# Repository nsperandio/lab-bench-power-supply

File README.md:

# lab-bench-power-supply (Work in progress, not ready yet).
A lab bench power supply made with a switching pre-regulation stage (tracking) followed by a custom linear regulator.

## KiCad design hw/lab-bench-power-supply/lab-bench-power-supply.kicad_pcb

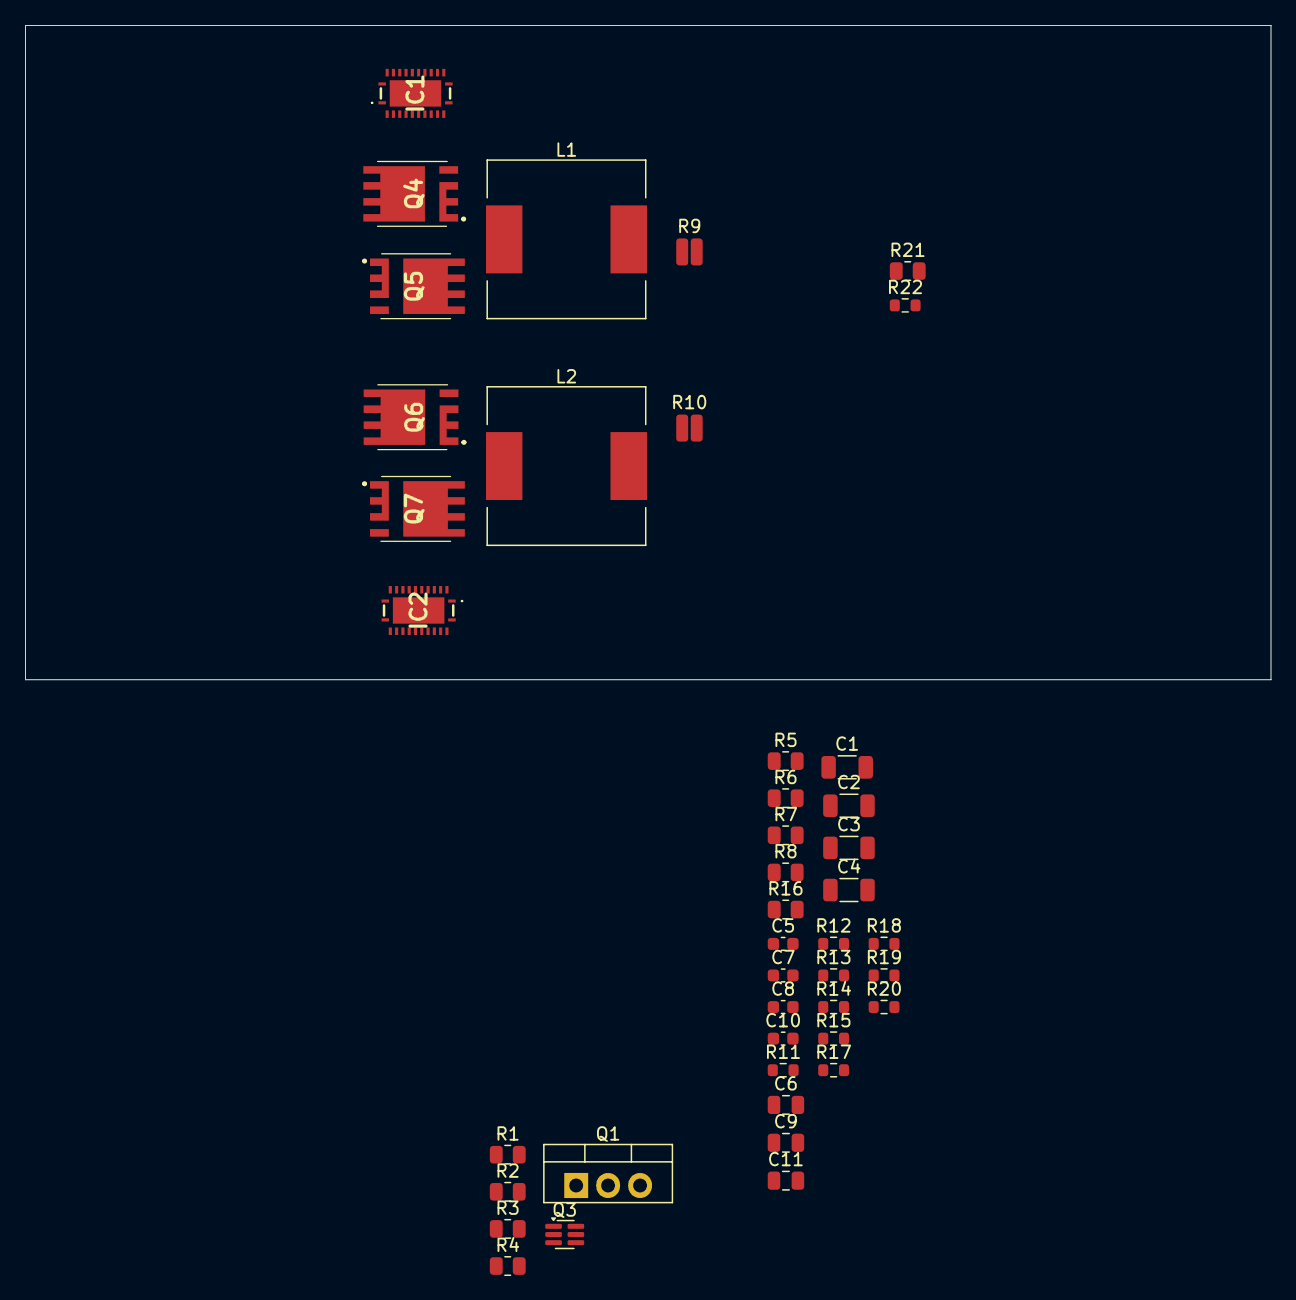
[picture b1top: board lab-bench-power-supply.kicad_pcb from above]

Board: 2 copper layers, 99.0 x 52.0 mm, 43 parts (0 on the bottom side), 36 nets, no tracks yet.

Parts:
C1, C2, C3, C4: C; C_1206_3216Metric
C5, C7, C8, C10: 0.1; C_0603_1608Metric
C6, C9: 0.1u; C_0805_2012Metric
C11: 2.2u; C_0805_2012Metric
IC1, IC2: LM5148RGYR
L1, L2: 47uH; L_12x12mm_H6mm
Q1: TIP42C; TO-220-3_Vertical
Q3: BC856BS; SOT-363_SC-70-6
Q4, Q5, Q6, Q7: BSC019N06NS; IPC100N04S51R2ATMA1
R1, R2, R3, R4: R; R_0805_2012Metric
R5, R6, R7, R8: 2.2; R_0805_2012Metric
R9, R10: 8m; R_0508_1220Metric
R11, R12, R13, R22: R; R_0603_1608Metric
R14: 54.9k; R_0603_1608Metric
R15: 90.0k; R_0603_1608Metric
R16, R21: 10k; R_0805_2012Metric
R17, R19: 100k; R_0603_1608Metric
R18, R20: 10k; R_0603_1608Metric

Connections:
/Buck/CBOOT1: C5.1, IC1.15 (CBOOT)
/Buck/CBOOT2: C10.1, IC2.15 (CBOOT)
/Buck/CNFG1: IC1.3 (CNFG), R14.1
/Buck/CNFG2: IC2.3 (CNFG), R15.1
/Buck/EXTCOMP: IC1.5 (EXTCOMP), IC2.5 (EXTCOMP)
/Buck/FB: IC1.6 (FB), R11.2, R12.2, R13.1, R22.2
/Buck/GH1: IC1.13 (HO), R5.1, R7.1
/Buck/GL1: IC1.11 (LO), R6.1, R8.1
/Buck/RT1: IC1.4 (RT), R17.1
/Buck/RT2: IC2.4 (RT), R19.1
/Buck/SW1: C5.2, IC1.14 (SW), L1.1, Q4.1, Q4.2 (S_2), Q4.3 (S_3), Q4.10 (S_4), Q5.5, Q5.6 (D_2), Q5.7 (D_3), Q5.8 (D_4), Q5.9 (D_5)
/Buck/SW2: C10.2, IC2.14 (SW)
/Buck/SYNC: IC1.17 (PG/SYNCOUT), IC2.18 (PFM/SYNC)
/Buck/VIN_BUCK: IC1.12 (VIN), IC2.12 (VIN), Q4.5, Q4.6 (D_2), Q4.7 (D_3), Q4.8 (D_4), Q4.9 (D_5), Q6.5, Q6.6 (D_2), Q6.7 (D_3), Q6.8 (D_4), Q6.9 (D_5), R16.1, R21.1
/Buck/VLINK: C1.1, C2.1, C3.1, C4.1, R9.2, R10.2, R12.1
GND: C1.2, C2.2, C3.2, C4.2, C6.2, C7.1, C8.1, C9.2, C11.2, IC1.7 (AGND_1), IC1.10 (PGND), IC1.18 (PFM/SYNC), IC1.25 (AGND_2), IC2.6 (FB), IC2.7 (AGND_1), IC2.10 (PGND), IC2.25 (AGND_2), Q5.1, Q5.2 (S_2), Q5.3 (S_3), Q5.10 (S_4), Q7.1, Q7.2 (S_2), Q7.3 (S_3), Q7.10 (S_4), R4.2, R13.2, R14.2, R15.2, R18.2, R20.2
unnamed: Q3.3 (C2), R2.1, R4.1
unnamed: IC1.19 (EN), R16.2
unnamed: C11.1, IC1.9 (VCC)
unnamed: C8.2, IC1.16 (VCCX)
unnamed: IC2.19 (EN), R21.2
unnamed: C7.2, IC2.16 (VCCX)
unnamed: L1.2, R9.1
unnamed: L2.2, R10.1
unnamed: Q1.1 (B), Q3.6 (C1)
unnamed: Q1.2 (C), R1.1
unnamed: Q3.1 (E1), R1.2
unnamed: Q3.4 (E2), R3.2
unnamed: Q4.4, R5.2
unnamed: Q5.4, R6.2
unnamed: Q6.4, R7.2
unnamed: L2.1, Q6.1, Q6.2 (S_2), Q6.3 (S_3), Q6.10 (S_4), Q7.5, Q7.6 (D_2), Q7.7 (D_3), Q7.8 (D_4), Q7.9 (D_5)
unnamed: Q7.4, R8.2
unnamed: R17.2, R18.1
unnamed: R19.2, R20.1
VDDA: C6.1, C9.1, IC1.8 (VDDA), IC2.8 (VDDA), R11.1

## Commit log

2026-02-21 Added simetrix sim of the linear regulator (WIP). Added Kicad project (WIP)
2026-02-24 Added Simetrix / Simplis dual phase buck design
